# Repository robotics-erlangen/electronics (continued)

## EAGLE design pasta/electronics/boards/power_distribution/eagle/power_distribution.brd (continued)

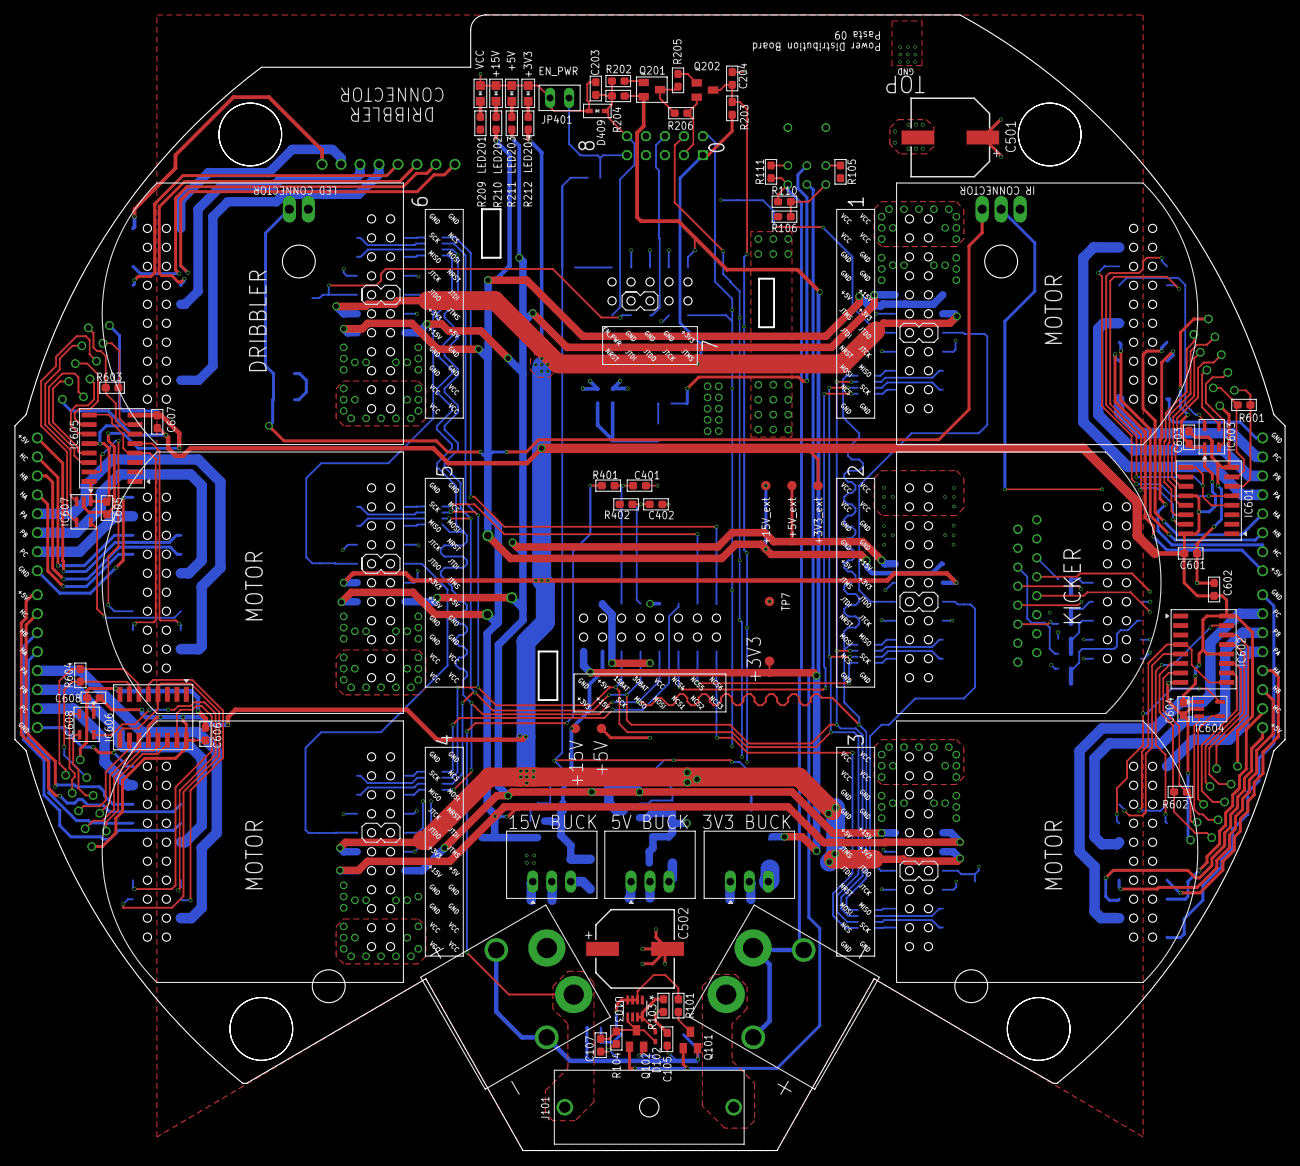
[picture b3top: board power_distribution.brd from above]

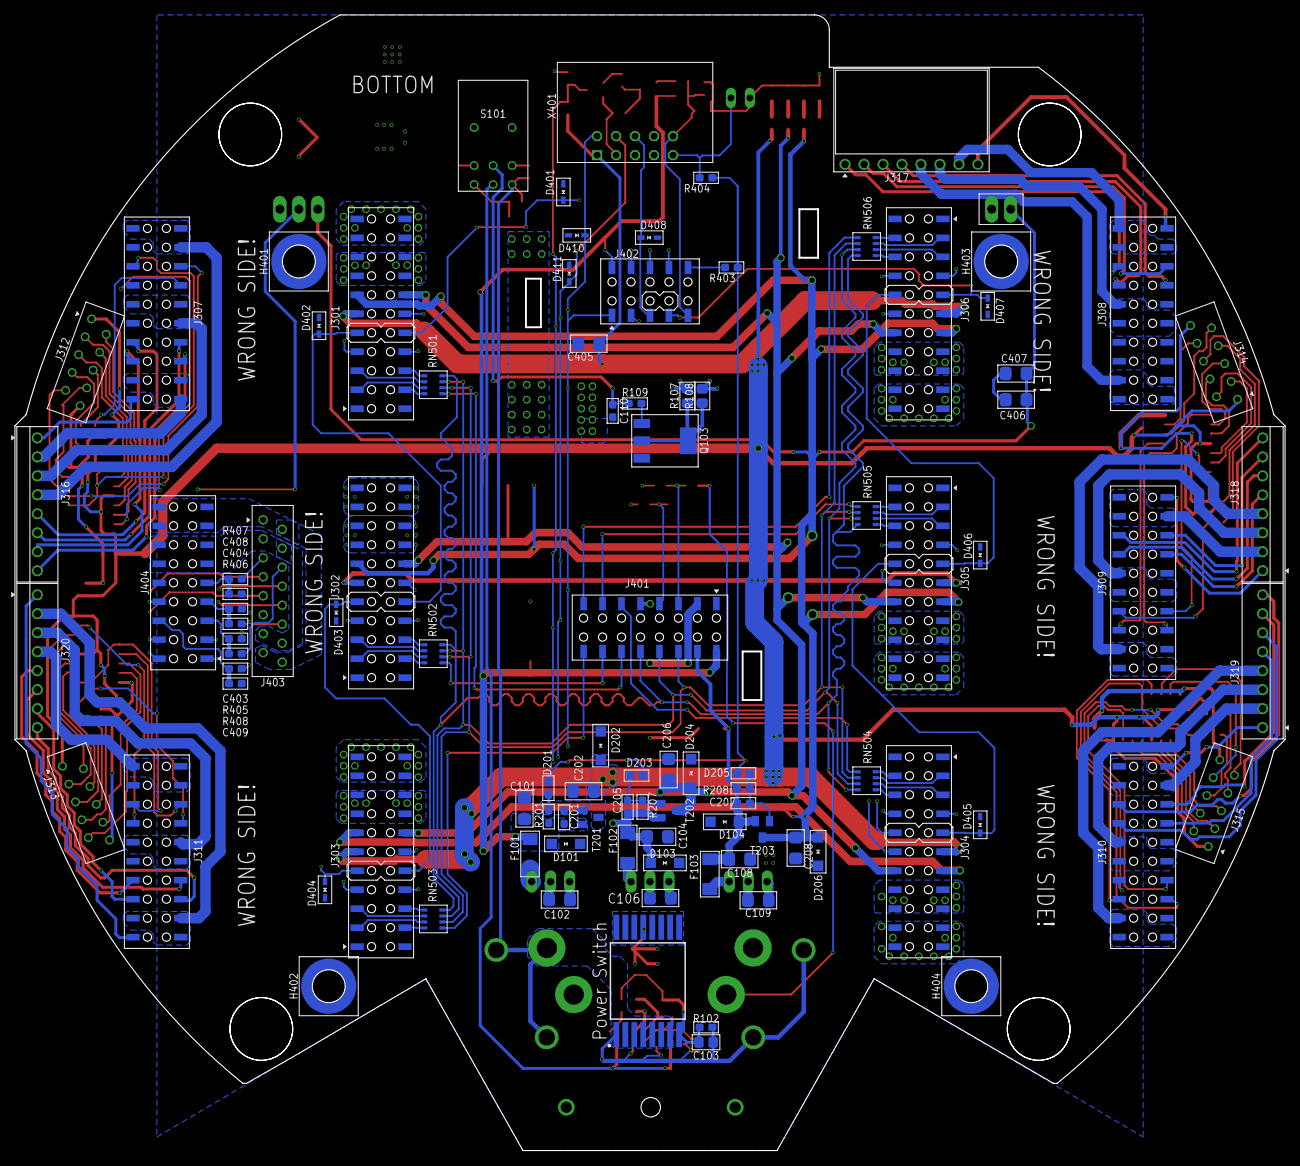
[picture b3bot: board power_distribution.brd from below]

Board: 4 copper layers, 170.0 x 152.0 mm, 170 parts (99 on the bottom side), 188 nets.

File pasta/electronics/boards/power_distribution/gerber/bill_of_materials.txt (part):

Stückliste exportiert aus D:/hardware/pasta/electronics/boards/power_distribution/eagle/power_distribution.sch am 04.07.2023 15:23

Part   Value                   Device                         Package                  Description                                                                     CAPACITANCE DATASHEET-URL                                                DF  DIAMETER DIELECTRIC I-LEAK I-RIPPLE L      LINE1     LINE2       MF                    MOUSER                MPN                 OPERATING-TEMPERATURE PART-NUMBER    POWER   RESISTANCE TECHNICAL-REFERENCE     TOLERANCE VALUE                VDS VOLTAGE VR      Z      
C101   10u ±20% 50V X5R        C(10UF,50V,1206)               C1206                    Robotics Erlangen Capacitor Library                                             10u                                                                                   X5R                               10u ±20%  50V X5R     Samsung                                     CL31A106MBHNNNE                                                                                     ±20%      10u ±20% 50V X5R         50V                    
C102   10u ±20% 50V X5R        C(10UF,50V,1206)               C1206                    Robotics Erlangen Capacitor Library                                             10u                                                                                   X5R                               10u ±20%  50V X5R     Samsung                                     CL31A106MBHNNNE                                                                                     ±20%      10u ±20% 50V X5R         50V                    
C103   4u7 ±10% 50V X5R        C(4.7UF,50V,0805)              C0805                    Robotics Erlangen Capacitor Library                                             4u7                                                                                   X5R                               4u7 ±10%  50V X5R     Samsung                                     CL21A475KBQNNNE                                                                                     ±10%      4u7 ±10% 50V X5R         50V                    
C104   10u ±20% 50V X5R        C(10UF,50V,1206)               C1206                    Robotics Erlangen Capacitor Library                                             10u                                                                                   X5R                               10u ±20%  50V X5R     Samsung                                     CL31A106MBHNNNE                                                                                     ±20%      10u ±20% 50V X5R         50V                    
C105   1u ±10% 50V X5R         C(1.0UF,50V,0603)              C0603                    Robotics Erlangen Capacitor Library                                             1u                                                                                    X5R                               1u ±10%   50V X5R     Samsung                                     CL10A105KB8NNNC                                                                                     ±10%      1u ±10% 50V X5R          50V                    
C106   10u ±20% 50V X5R        C(10UF,50V,1206)               C1206                    Robotics Erlangen Capacitor Library                                             10u                                                                                   X5R                               10u ±20%  50V X5R     Samsung                                     CL31A106MBHNNNE                                                                                     ±20%      10u ±20% 50V X5R         50V                    
C107   10n ±10% 50V X7R        C(10NF,50V,0603)               C0603                    Robotics Erlangen Capacitor Library                                             10n                                                                                   X7R                               10n ±10%  50V X7R     Würth Elektronik                            885012206089                                                                                        ±10%      10n ±10% 50V X7R         50V                    
C108   10u ±20% 50V X5R        C(10UF,50V,1206)               C1206                    Robotics Erlangen Capacitor Library                                             10u                                                                                   X5R                               10u ±20%  50V X5R     Samsung                                     CL31A106MBHNNNE                                                                                     ±20%      10u ±20% 50V X5R         50V                    
C109   10u ±20% 50V X5R        C(10UF,50V,1206)               C1206                    Robotics Erlangen Capacitor Library                                             10u                                                                                   X5R                               10u ±20%  50V X5R     Samsung                                     CL31A106MBHNNNE                                                                                     ±20%      10u ±20% 50V X5R         50V                    
C110   470n ±10% 25V X7R       C(470NF,25V,0603)              C0603                    Robotics Erlangen Capacitor Library                                             470n                                                                                  X7R                               470n ±10% 25V X7R     Würth Elektronik                            885012206075                                                                                        ±10%      470n ±10% 25V X7R        25V                    
C201   100n ±10% 50V X7R       C(100NF,50V,0603)              C0603                    Robotics Erlangen Capacitor Library                                             100n                                                                                  X7R                               100n ±10% 50V X7R     Würth Elektronik                            885012206095                                                                                        ±10%      100n ±10% 50V X7R        50V                    
C202   10u ±20% 50V X5R        C(10UF,50V,1206)               C1206                    Robotics Erlangen Capacitor Library                                             10u                                                                                   X5R                               10u ±20%  50V X5R     Samsung                                     CL31A106MBHNNNE                                                                                     ±20%      10u ±20% 50V X5R         50V                    
C203   10n ±10% 50V X7R        C(10NF,50V,0603)               C0603                    Robotics Erlangen Capacitor Library                                             10n                                                                                   X7R                               10n ±10%  50V X7R     Würth Elektronik                            885012206089                                                                                        ±10%      10n ±10% 50V X7R         50V                    
C204   470n ±10% 50V X7R       C(470NF,50V,0603)              C0603                    Robotics Erlangen Capacitor Library                                             470n                                                                                  X7R                               470n ±10% 50V X7R     Taiyo Yuden                                 UMK107B7474KA-TR                                                                                    ±10%      470n ±10% 50V X7R        50V                    
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
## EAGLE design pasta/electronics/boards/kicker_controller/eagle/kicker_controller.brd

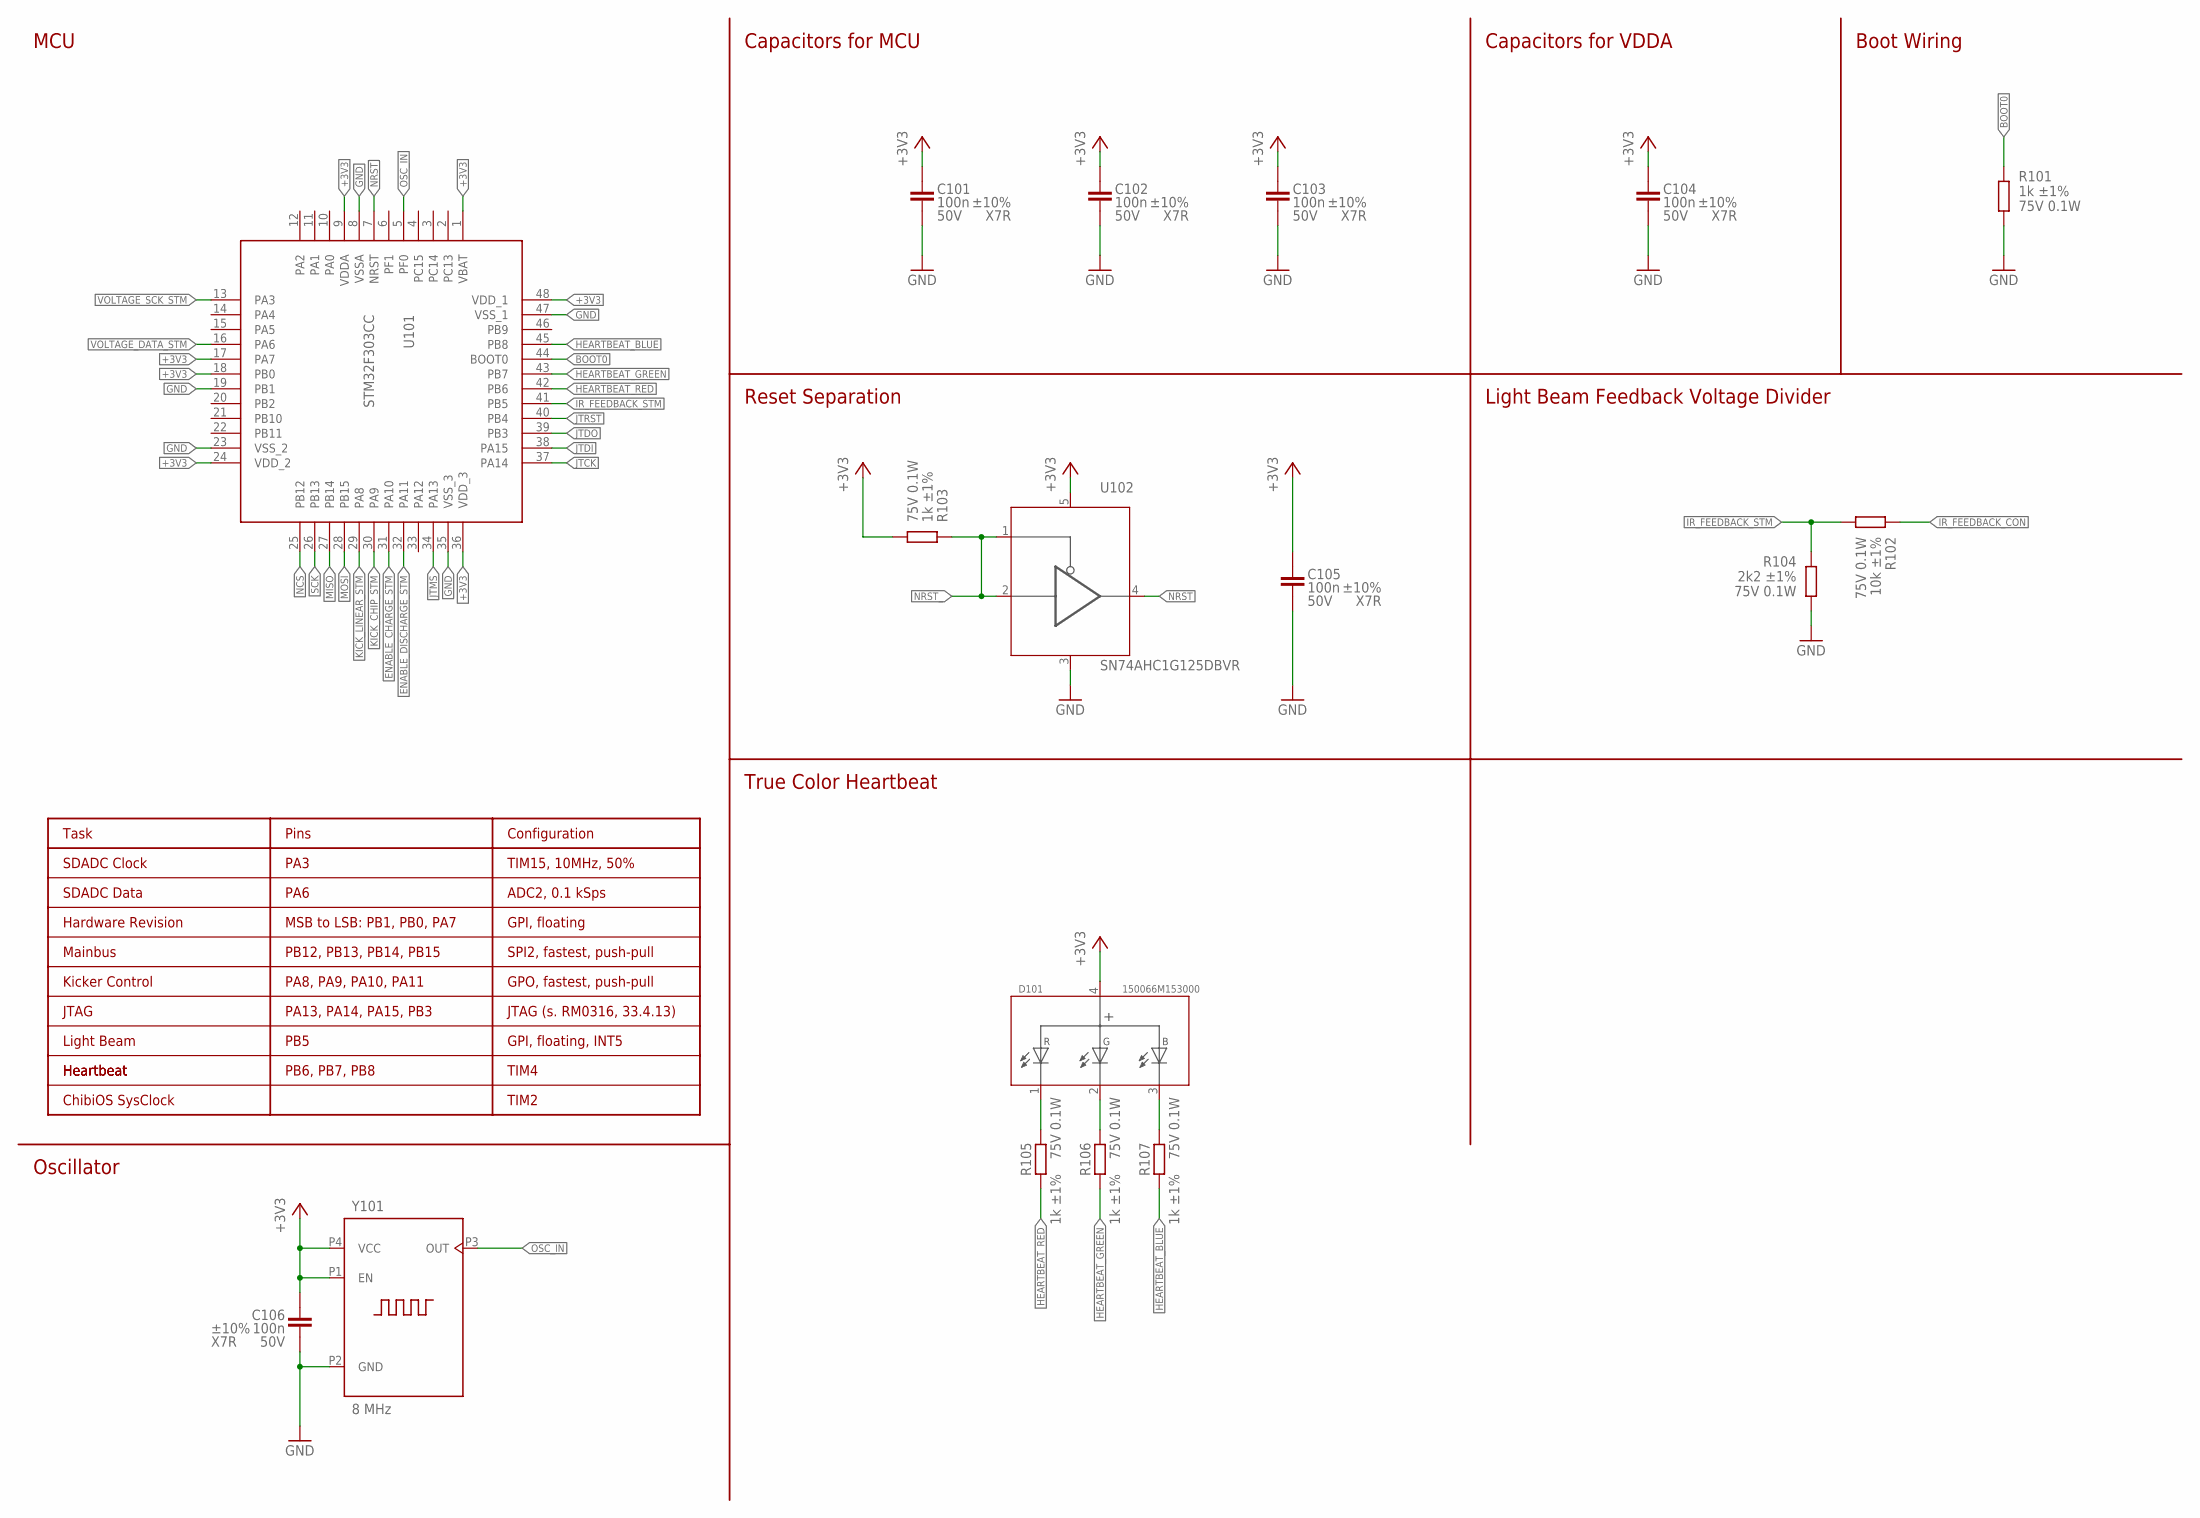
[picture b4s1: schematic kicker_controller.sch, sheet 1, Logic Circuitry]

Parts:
C101, C102, C103, C104, C105, C106: 100n ±10% 50V X7R; C0603
D101: 150066M153000; WL-SFCX_0606
R101, R103, R105, R106, R107: 1k ±1% 75V 0.1W; R0603
R102: 10k ±1% 75V 0.1W; R0603
R104: 2k2 ±1% 75V 0.1W; R0603
U101: STM32F303CC; LQFP48
U102: SN74AHC1G125DBVR; SOT23-5
Y101: 8 MHz; 830207192009

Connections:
+3V3: C101.1, C102.1, C103.1, C104.1, C105.1, C106.1, D101.4, R103.1, U101.1 (VBAT), U101.9 (VDDA), U101.17 (PA7), U101.18 (PB0), U101.24 (VDD_2), U101.36 (VDD_3), U101.48 (VDD_1), U102.5 (VCC), Y101.P1 (EN), Y101.P4 (VCC); also elsewhere on the board
BOOT0: R101.2, U101.44 (BOOT0)
ENABLE_CHARGE_STM: U101.31 (PA10); also elsewhere on the board
ENABLE_DISCHARGE_STM: U101.32 (PA11); also elsewhere on the board
GND: C101.2, C102.2, C103.2, C104.2, C105.2, C106.2, R101.1, R104.1, U101.8 (VSSA), U101.19 (PB1), U101.23 (VSS_2), U101.35 (VSS_3), U101.47 (VSS_1), U102.3 (GND), Y101.P2 (GND); also elsewhere on the board
HEARTBEAT_BLUE: R107.2, U101.45 (PB8)
HEARTBEAT_GREEN: R106.2, U101.43 (PB7)
HEARTBEAT_RED: R105.2, U101.42 (PB6)
IR_FEEDBACK_CON: R102.2; also elsewhere on the board
IR_FEEDBACK_STM: R102.1, R104.2, U101.41 (PB5)
JTCK: U101.37 (PA14); also elsewhere on the board
JTDI: U101.38 (PA15); also elsewhere on the board
JTDO: U101.39 (PB3); also elsewhere on the board
JTMS: U101.34 (PA13); also elsewhere on the board
JTRST: U101.40 (PB4)
KICK_CHIP_STM: U101.30 (PA9); also elsewhere on the board
KICK_LINEAR_STM: U101.29 (PA8); also elsewhere on the board
MISO: U101.27 (PB14); also elsewhere on the board
MOSI: U101.28 (PB15); also elsewhere on the board
unnamed: D101.1 (R), R105.1
unnamed: D101.2 (G), R106.1
unnamed: D101.3 (B), R107.1
NCS: U101.25 (PB12); also elsewhere on the board
NRST: U101.7 (NRST), U102.4 (O)
NRST_: R103.2, U102.1 (OE), U102.2 (I); also elsewhere on the board
OSC_IN: U101.5 (PF0), Y101.P3 (OUT)
SCK: U101.26 (PB13); also elsewhere on the board
VOLTAGE_DATA_STM: U101.16 (PA6); also elsewhere on the board
VOLTAGE_SCK_STM: U101.13 (PA3); also elsewhere on the board

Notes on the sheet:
Light Beam Feedback Voltage Divider
Oscillator
True Color Heartbeat
Reset Separation
MCU
Capacitors for MCU
Capacitors for VDDA
Boot Wiring
Task
Pins
Configuration
SDADC Clock
SDADC Data
Hardware Revision
Mainbus
MSB to LSB: PB1, PB0, PA7
PB12, PB13, PB14, PB15
PA6
PA3
TIM15, 10MHz, 50%
ADC2, 0.1 kSps
GPI, floating
SPI2, fastest, push-pull
Light Beam
PB5
GPI, floating, INT5
Heartbeat
PB6, PB7, PB8
JTAG
PA13, PA14, PA15, PB3
JTAG (s. RM0316, 33.4.13)
Kicker Control
PA8, PA9, PA10, PA11
GPO, fastest, push-pull
TIM4
ChibiOS SysClock
TIM2

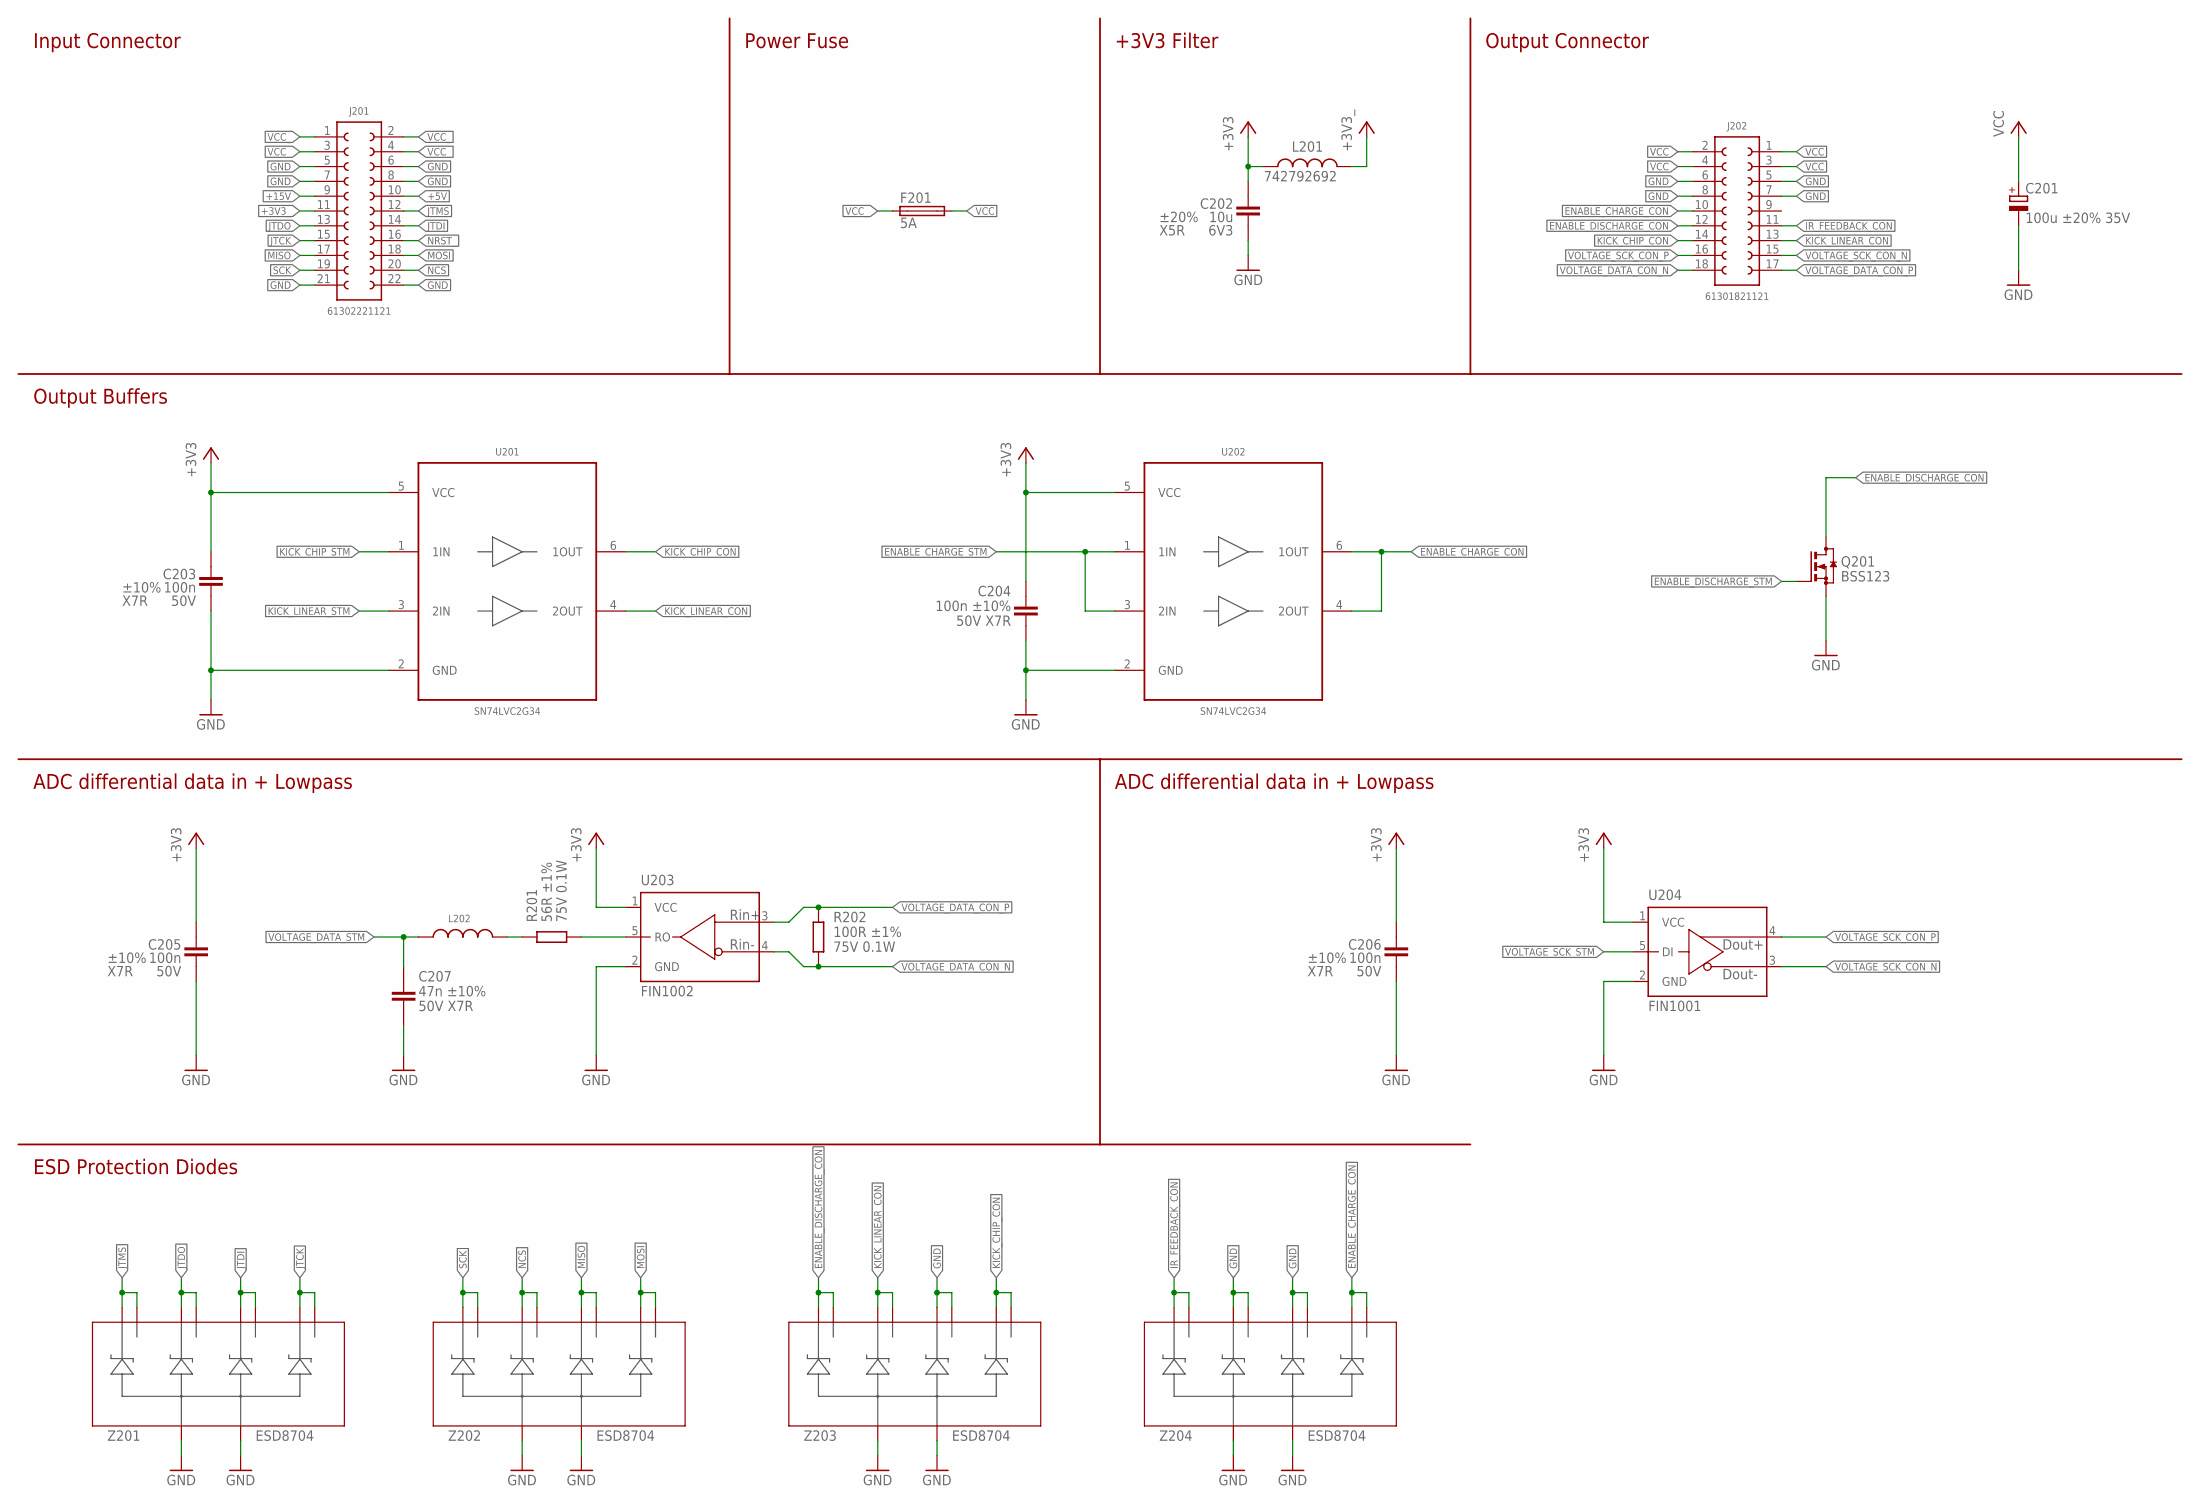
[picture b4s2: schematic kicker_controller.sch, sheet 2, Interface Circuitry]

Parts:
C201: 100u ±20% 35V; 865080545012
C202: 10u ±20% 6V3 X5R; C0603
C203, C204, C205, C206: 100n ±10% 50V X7R; C0603
C207: 47n ±10% 50V X7R; C0603
F201: 5A; 157T
J201: 61302221121
J202: 61301821121
L201: 742792692; WE-CBF_0603(W=2.6)
L202: WE-GFH_4532_7447669212; WE-GFH_4532
Q201: BSS123; SOT23
R201: 56R ±1% 75V 0.1W; R0603
R202: 100R ±1% 75V 0.1W; R0603
U201, U202: SN74LVC2G34; SOT
U203: FIN1002; SOT23-5
U204: FIN1001; SOT23-5
Z201, Z202, Z203, Z204: ESD8704; UDFN10

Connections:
+3V3: C202.1, C203.1, C204.1, C205.1, C206.1, L201.2, U201.5 (VCC), U202.5 (VCC), U203.1 (VCC), U204.1 (VCC); also elsewhere on the board
+3V3_: J201.11, L201.1
+5V: J201.10
+15V: J201.9
ENABLE_CHARGE_CON: J202.10, U202.4 (2OUT), U202.6 (1OUT), Z204.5 (C4), Z204.6 (D4)
ENABLE_CHARGE_STM: U202.1 (1IN), U202.3 (2IN); also elsewhere on the board
ENABLE_DISCHARGE_CON: J202.12, Q201.3 (D), Z203.1 (C1), Z203.10 (D1)
ENABLE_DISCHARGE_STM: Q201.1 (G); also elsewhere on the board
GND: C201.N (-), C202.2, C203.2, C204.2, C205.2, C206.2, C207.2, J201.5, J201.6, J201.7, J201.8, J201.21, J201.22, J202.5, J202.6, J202.7, J202.8, Q201.2 (S), U201.2 (GND), U202.2 (GND), U203.2 (GND), U204.2 (GND), Z201.3 (A), Z201.8 (A), Z202.3 (A), Z202.8 (A), Z203.3 (A), Z203.4 (C3), Z203.7 (D3), Z203.8 (A), Z204.2 (C2), Z204.3 (A), Z204.4 (C3), Z204.7 (D3), Z204.8 (A), Z204.9 (D2); also elsewhere on the board
IR_FEEDBACK_CON: J202.11, Z204.1 (C1), Z204.10 (D1); also elsewhere on the board
JTCK: J201.15, Z201.5 (C4), Z201.6 (D4); also elsewhere on the board
JTDI: J201.14, Z201.4 (C3), Z201.7 (D3); also elsewhere on the board
JTDO: J201.13, Z201.2 (C2), Z201.9 (D2); also elsewhere on the board
JTMS: J201.12, Z201.1 (C1), Z201.10 (D1); also elsewhere on the board
KICK_CHIP_CON: J202.14, U201.6 (1OUT), Z203.5 (C4), Z203.6 (D4)
KICK_CHIP_STM: U201.1 (1IN); also elsewhere on the board
KICK_LINEAR_CON: J202.13, U201.4 (2OUT), Z203.2 (C2), Z203.9 (D2)
KICK_LINEAR_STM: U201.3 (2IN); also elsewhere on the board
MISO: J201.17, Z202.4 (C3), Z202.7 (D3); also elsewhere on the board
MOSI: J201.18, Z202.5 (C4), Z202.6 (D4); also elsewhere on the board
unnamed: R201.1, U203.5 (RO)
unnamed: L202.2, R201.2
NCS: J201.20, Z202.2 (C2), Z202.9 (D2); also elsewhere on the board
NRST_: J201.16; also elsewhere on the board
SCK: J201.19, Z202.1 (C1), Z202.10 (D1); also elsewhere on the board
VCC: C201.P (+), F201.2, J202.1, J202.2, J202.3, J202.4
VCC_: F201.1, J201.1, J201.2, J201.3, J201.4
VOLTAGE_DATA_CON_N: J202.18, R202.1, U203.4 (RIN-)
VOLTAGE_DATA_CON_P: J202.17, R202.2, U203.3 (RIN+)
VOLTAGE_DATA_STM: C207.1, L202.1; also elsewhere on the board
VOLTAGE_SCK_CON_N: J202.15, U204.3 (DOUT-)
VOLTAGE_SCK_CON_P: J202.16, U204.4 (DOUT+)
VOLTAGE_SCK_STM: U204.5 (DI); also elsewhere on the board

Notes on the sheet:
Input Connector
ESD Protection Diodes
Power Fuse
+3V3 Filter
Output Connector
ADC differential data in + Lowpass
Output Buffers

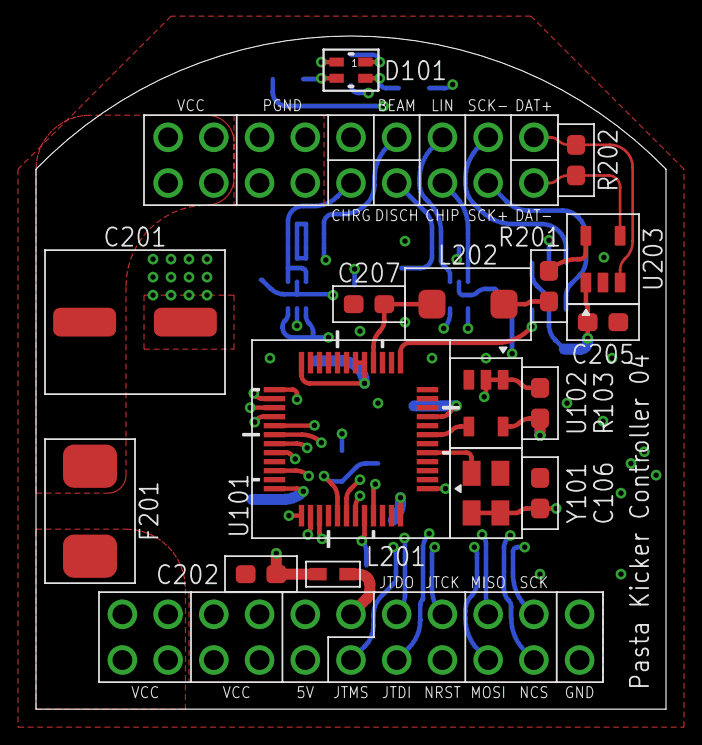
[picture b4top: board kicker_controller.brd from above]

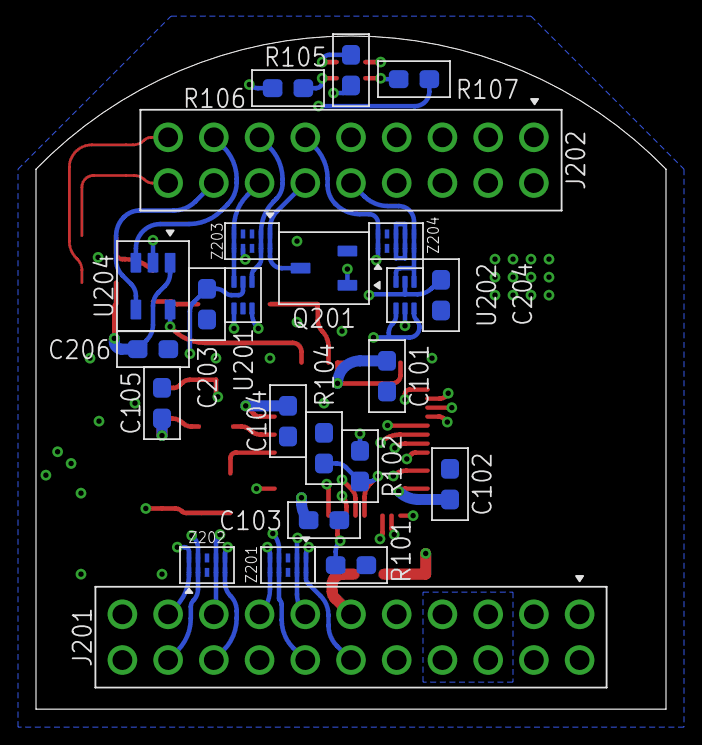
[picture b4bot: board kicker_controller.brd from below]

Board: 4 copper layers, 35.0 x 37.4 mm, 40 parts (24 on the bottom side), 41 nets.

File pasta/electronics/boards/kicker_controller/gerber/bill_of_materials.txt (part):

Stückliste exportiert aus D:/hardware/pasta/electronics/boards/kicker_controller/eagle/kicker_controller.sch am 04.07.2023 12:30

Part Value             Device                 Package            Description                                              CAPACITANCE DIELECTRIC LINE1     LINE2    MF                 MOUSER               MOUSER-NR      MPN              POPULARITY POWER RESISTANCE TOLERANCE VALUE             VOLTAGE WE-NUMBER       
C101 100n ±10% 50V X7R C(100NF,50V,0603)      C0603              Robotics Erlangen Capacitor Library                      100n        X7R        100n ±10% 50V X7R  Würth Elektronik                                       885012206095                                 ±10%      100n ±10% 50V X7R 50V                     
C102 100n ±10% 50V X7R C(100NF,50V,0603)      C0603              Robotics Erlangen Capacitor Library                      100n        X7R        100n ±10% 50V X7R  Würth Elektronik                                       885012206095                                 ±10%      100n ±10% 50V X7R 50V                     
C103 100n ±10% 50V X7R C(100NF,50V,0603)      C0603              Robotics Erlangen Capacitor Library                      100n        X7R        100n ±10% 50V X7R  Würth Elektronik                                       885012206095                                 ±10%      100n ±10% 50V X7R 50V                     
C104 100n ±10% 50V X7R C(100NF,50V,0603)      C0603              Robotics Erlangen Capacitor Library                      100n        X7R        100n ±10% 50V X7R  Würth Elektronik                                       885012206095                                 ±10%      100n ±10% 50V X7R 50V                     
C105 100n ±10% 50V X7R C(100NF,50V,0603)      C0603              Robotics Erlangen Capacitor Library                      100n        X7R        100n ±10% 50V X7R  Würth Elektronik                                       885012206095                                 ±10%      100n ±10% 50V X7R 50V                     
C106 100n ±10% 50V X7R C(100NF,50V,0603)      C0603              Robotics Erlangen Capacitor Library                      100n        X7R        100n ±10% 50V X7R  Würth Elektronik                                       885012206095                                 ±10%      100n ±10% 50V X7R 50V                     
C201 100u ±20% 35V     865080545012           865080545012                                                                                                          Würth Elektronik                                       865080545012                                           100u ±20% 35V                             
C202 10u ±20% 6V3 X5R  C(10UF,6.3V,0603)      C0603              Robotics Erlangen Capacitor Library                      10u         X5R        10u ±20%  6V3 X5R  Würth Elektronik                                       885012106006                                 ±20%      10u ±20% 6V3 X5R  6V3                     
C203 100n ±10% 50V X7R C(100NF,50V,0603)      C0603              Robotics Erlangen Capacitor Library                      100n        X7R        100n ±10% 50V X7R  Würth Elektronik                                       885012206095                                 ±10%      100n ±10% 50V X7R 50V                     
C204 100n ±10% 50V X7R C(100NF,50V,0603)      C0603              Robotics Erlangen Capacitor Library                      100n        X7R        100n ±10% 50V X7R  Würth Elektronik                                       885012206095                                 ±10%      100n ±10% 50V X7R 50V                     
C205 100n ±10% 50V X7R C(100NF,50V,0603)      C0603              Robotics Erlangen Capacitor Library                      100n        X7R        100n ±10% 50V X7R  Würth Elektronik                                       885012206095                                 ±10%      100n ±10% 50V X7R 50V                     
C206 100n ±10% 50V X7R C(100NF,50V,0603)      C0603              Robotics Erlangen Capacitor Library                      100n        X7R        100n ±10% 50V X7R  Würth Elektronik                                       885012206095                                 ±10%      100n ±10% 50V X7R 50V                     
C207 47n ±10% 50V X7R  C(47NF,50V,0603)       C0603              Robotics Erlangen Capacitor Library                      47n         X7R        47n ±10%  50V X7R  Würth Elektronik                                       885012206093                                 ±10%      47n ±10% 50V X7R  50V                     
D101 150066M153000     150066M153000          WL-SFCX_0606       WL-SFCD SMD Full-color Chip LED Diffused                                                           Würth Elektronik                                       150066M153000                                                                                    
F201 5A                0157005.DRT            157T               157T Series - Standard Nano2&reg; Fuse and Clip Assembly                                           Littelfuse         576-0157005.DRT                     0157005.DRT                                                                                      
J201 61302221121       61302221121            61302221121                                                                                                           Würth Elektronik                                       61302221121                                                                                      
J202 61301821121       61301821121            61301821121                                                                                                           Würth Elektronik                                       61301821121                                                                                      
L201 742792692         742792692              WE-CBF_0603(W=2.6) WE-CBF SMD EMI Suppression Ferrite Bead                                                            Würth Elektronik                                       742792692                                                                                        
L202                   WE-GFH_4532_7447669212 WE-GFH_4532        SMD RF Choke WE-GFH                                                                                                                                                                                                                        7447669212/120uH
Q201 BSS123            BSS123                 SOT23              N-CHANNEL MOS FET                                                                                                                                                          21                                                                              
R101 1k ±1% 75V 0.1W   R(1.0K,75V,0.1W,0603)  R0603              Robotics Erlangen Resistor Library                                              1k ±1%    75V 0.1W YAGEO                                                  RC0603FR-071KL              0.1W  1k         ±1%       1k ±1% 75V 0.1W   75V                     
R102 10k ±1% 75V 0.1W  R(10K,75V,0.1W,0603)   R0603              Robotics Erlangen Resistor Library                                              10k ±1%   75V 0.1W YAGEO                                                  RC0603FR-0710KL             0.1W  10k        ±1%       10k ±1% 75V 0.1W  75V                     
R103 1k ±1% 75V 0.1W   R(1.0K,75V,0.1W,0603)  R0603              Robotics Erlangen Resistor Library                                              1k ±1%    75V 0.1W YAGEO                                                  RC0603FR-071KL              0.1W  1k         ±1%       1k ±1% 75V 0.1W   75V                     
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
